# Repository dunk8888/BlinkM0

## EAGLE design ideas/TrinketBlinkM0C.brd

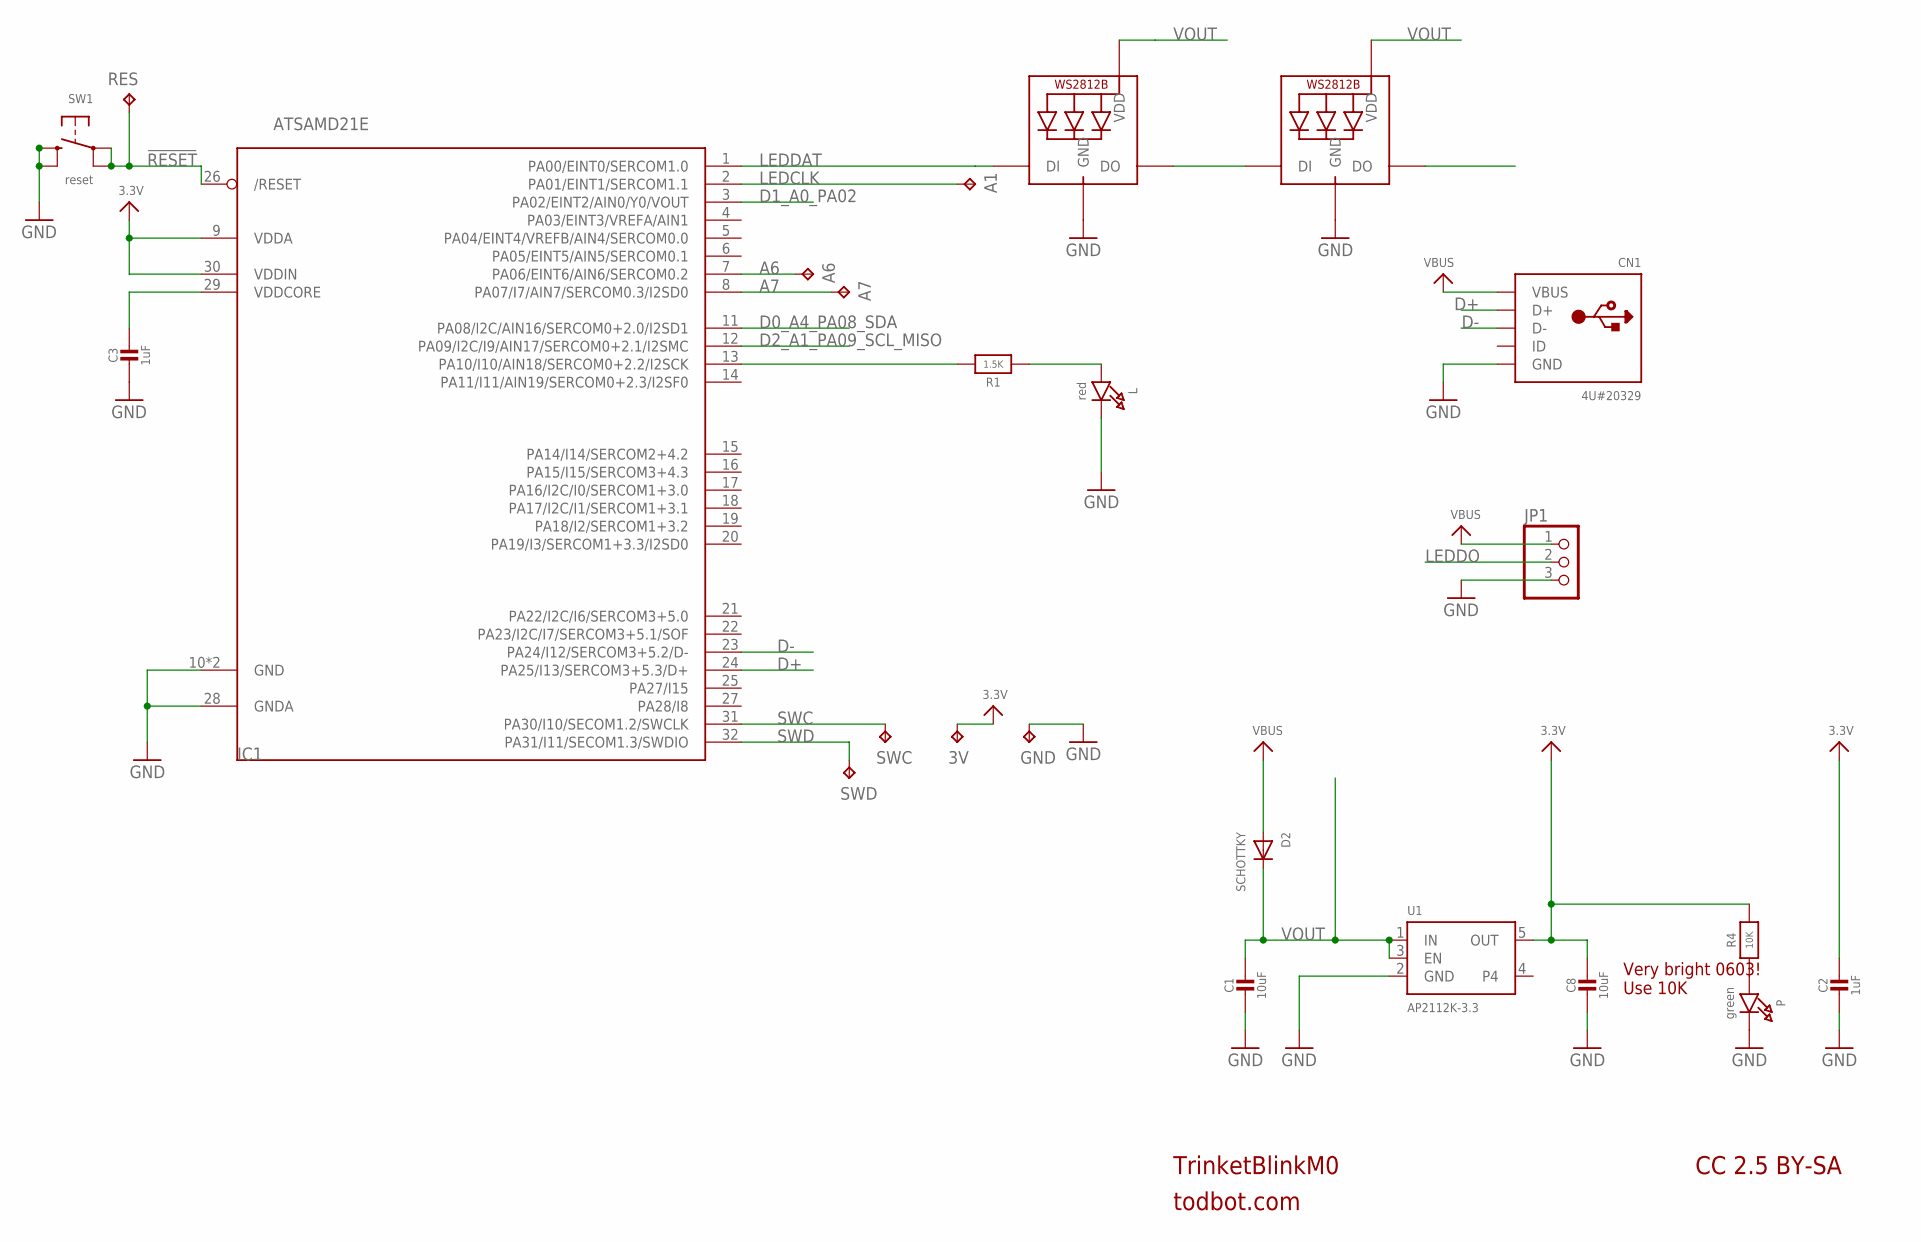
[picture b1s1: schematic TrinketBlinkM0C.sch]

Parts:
3V: TPB1,27; B1,27
A1, A6, A7: TPB1,27; B1,27
C1, C8: 10uF; 0805-NO
C2, C3: 1uF; 0603-NO
CN1: 4U#20329; 4UCONN_20329_V2
D2: SCHOTTKY; SOD-123FL
GND: TPB1,27; B1,27
IC1: ATSAMD21E; QFN32_5MM
JP1: PINHD-1X3CB; 1X03-CLEANBIG
L: red; CHIPLED_0603_NOOUTLINE
LED1, LED2: WS2812B_5050N; WS2812B-NARROW
P: green; CHIPLED_0603_NOOUTLINE
R1: 1.5K; 0603-NO
R4: 10K; 0603-NO
RES: TPB1,27; B1,27
SW1: reset; BTN_KMR2_4.6X2.8
SWC: TPB1,27; B1,27
SWD: TPB1,27; B1,27
U1: AP2112K-3.3; SOT23-5

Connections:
3.3V: 3V.TP, C2.1, C8.1, IC1.9 (VDDA), IC1.30 (VDDIN), R4.2, U1.5 (OUT)
!RESET: IC1.26 (/RESET), RES.TP, SW1.A, SW1.A' (P1)
A6: A6.TP, IC1.7 (PA06/EINT6/AIN6/SERCOM0.2)
A7: A7.TP, IC1.8 (PA07/I7/AIN7/SERCOM0.3/I2SD0)
D0_A4_PA08_SDA: IC1.11 (PA08/I2C/AIN16/SERCOM0+2.0/I2SD1)
D1_A0_PA02: IC1.3 (PA02/EINT2/AIN0/Y0/VOUT)
D2_A1_PA09_SCL_MISO: IC1.12 (PA09/I2C/I9/AIN17/SERCOM0+2.1/I2SMC)
D+: CN1.D+, IC1.24 (PA25/I13/SERCOM3+5.3/D+)
D-: CN1.D-, IC1.23 (PA24/I12/SERCOM3+5.2/D-)
GND: C1.2, C2.2, C3.2, C8.2, CN1.BASE@1 (GND), CN1.BASE@2 (GND), CN1.GND, CN1.SPRT@1 (GND), CN1.SPRT@2 (GND), CN1.SPRT@3 (GND), CN1.SPRT@4 (GND), GND.TP, IC1.10 (GND), IC1.28 (GNDA), IC1.33 (GND), JP1.3, L.C, LED1.3-GND (GND), LED2.3-GND (GND), P.C, SW1.B (S), SW1.B' (S1), U1.2 (GND)
LEDCLK: A1.TP, IC1.2 (PA01/EINT1/SERCOM1.1)
LEDDAT: IC1.1 (PA00/EINT0/SERCOM1.0), LED1.4-DIN (DI)
LEDDO: JP1.2, LED2.2-DOUT (DO)
unnamed: L.A, R1.1
unnamed: IC1.13 (PA10/I10/AIN18/SERCOM0+2.2/I2SCK), R1.2
unnamed: LED1.2-DOUT (DO), LED2.4-DIN (DI)
unnamed: P.A, R4.1
SWC: IC1.31 (PA30/I10/SECOM1.2/SWCLK), SWC.TP
SWD: IC1.32 (PA31/I11/SECOM1.3/SWDIO), SWD.TP
VBUS: CN1.VBUS, D2.A, JP1.1
VDDCORE: C3.1, IC1.29 (VDDCORE)
VOUT: C1.1, D2.C, LED1.1-VDD (VDD), LED2.1-VDD (VDD), U1.1 (IN), U1.3 (EN)

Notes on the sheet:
TrinketBlinkM0
todbot.com
CC 2.5 BY-SA
Very bright 0603! Use 10K

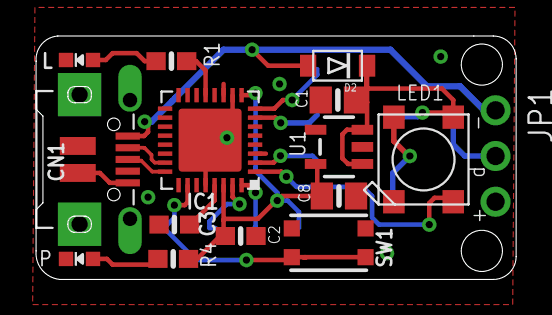
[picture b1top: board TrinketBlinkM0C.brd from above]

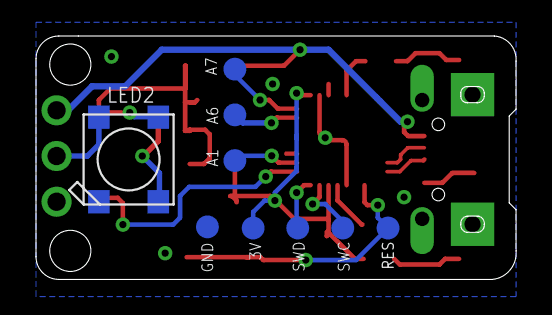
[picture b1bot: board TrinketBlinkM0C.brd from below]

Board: 2 copper layers, 26.7 x 13.5 mm, 26 parts (10 on the bottom side), 19 nets.

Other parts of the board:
U$1: TRINKET_M0_BOTTOM
U$20: TRINKET_M0_TOP

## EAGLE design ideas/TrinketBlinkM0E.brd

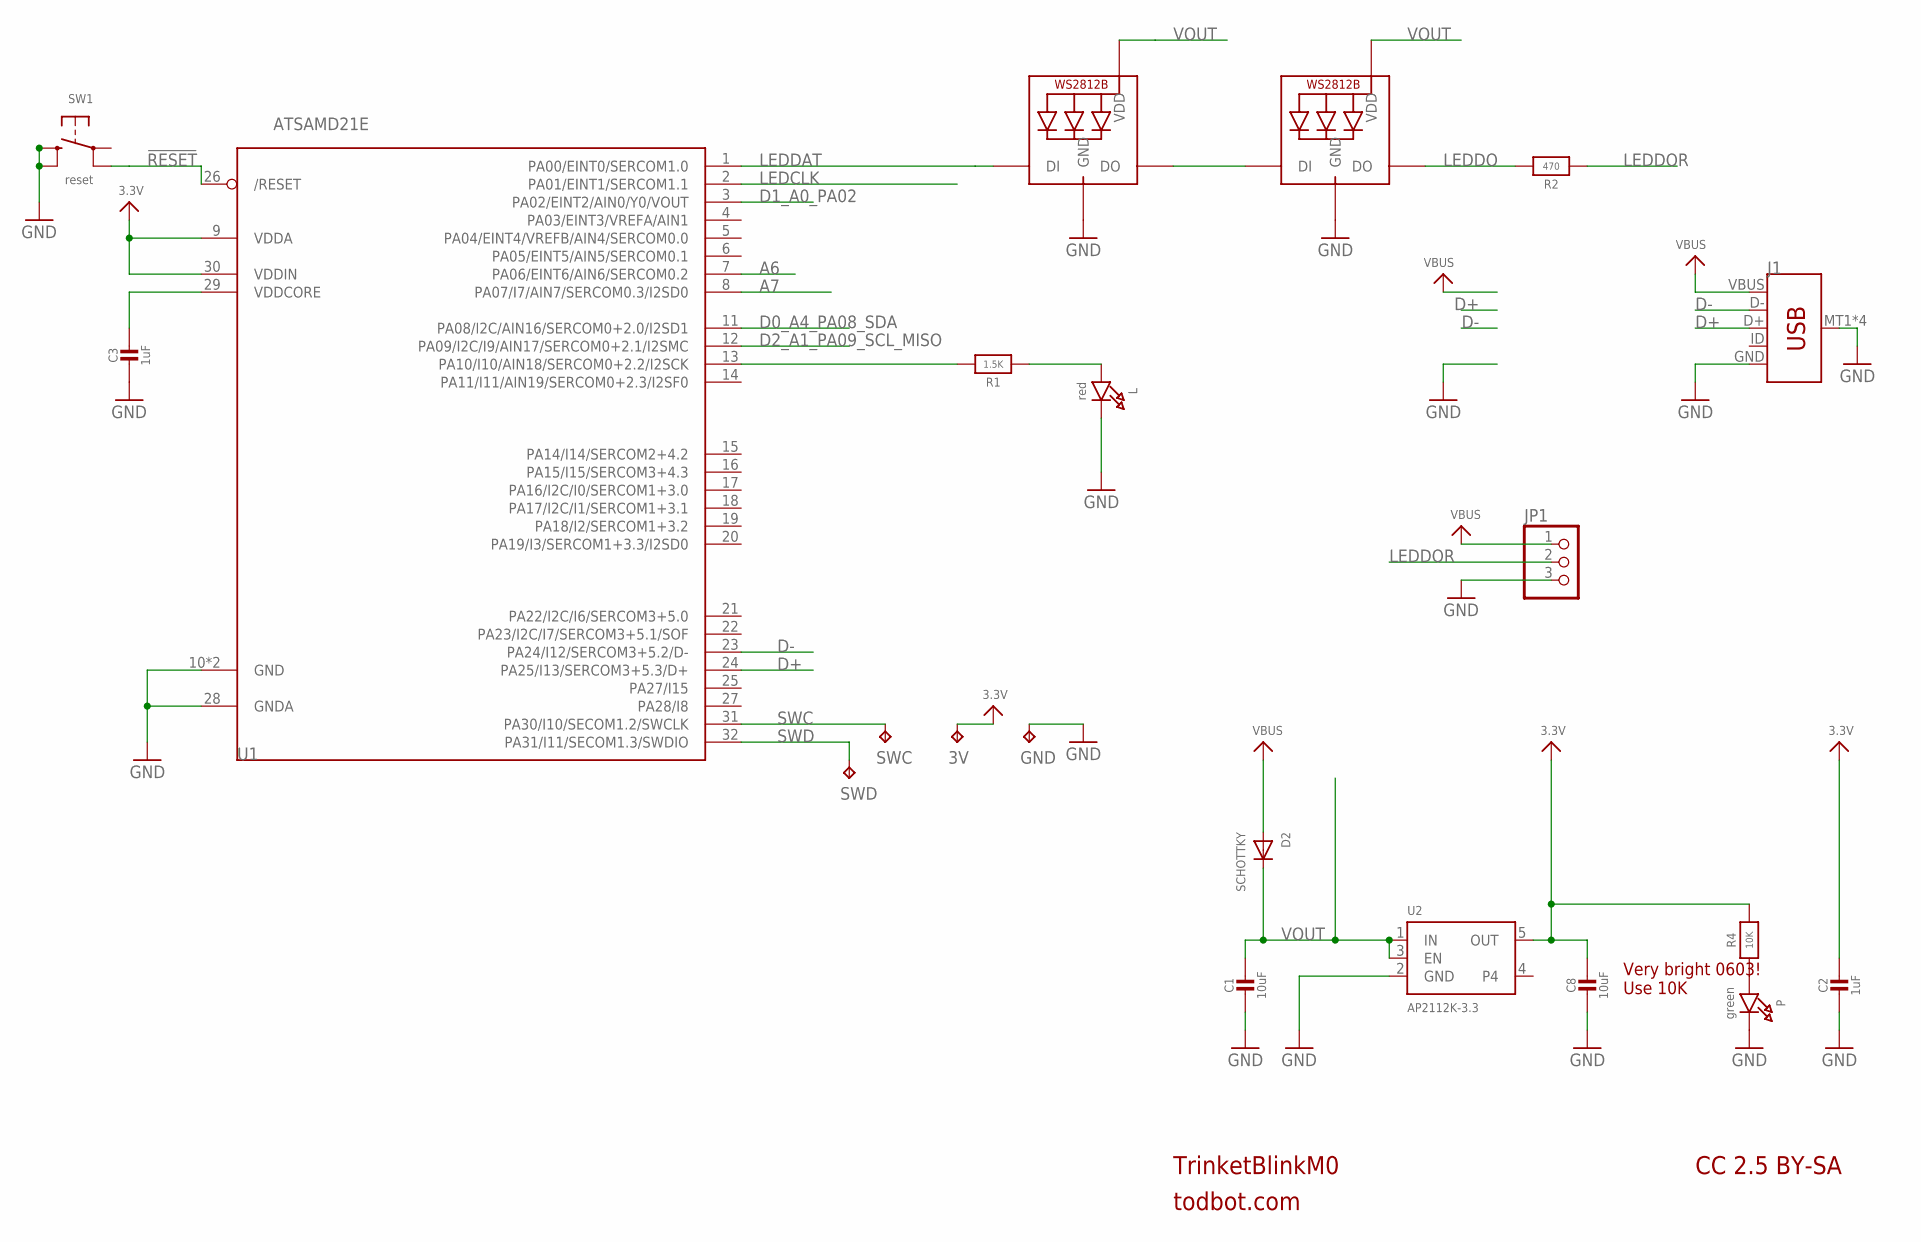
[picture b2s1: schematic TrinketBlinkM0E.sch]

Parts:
3V: TPB1,27; B1,27
C1, C8: 10uF; 0805-NO
C2, C3: 1uF; 0603-NO
D2: SCHOTTKY; SOD-123FL
GND: TPB1,27; B1,27
J1: USB_MICRO-B_SMT; USB-MICROB
JP1: PINHD-1X3CB; 1X03-CLEANBIG
L: red; CHIPLED_0603_NOOUTLINE
LED1, LED2: WS2812B_5050N; WS2812B-NARROW
P: green; CHIPLED_0603_NOOUTLINE
R1: 1.5K; 0603-NO
R2: 470; 0603-NO
R4: 10K; 0603-NO
SW1: reset; BTN_KMR2_4.6X2.8
SWC: TPB1,27; B1,27
SWD: TPB1,27; B1,27
U1: ATSAMD21E; QFN32_5MM
U2: AP2112K-3.3; SOT23-5

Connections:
3.3V: 3V.TP, C2.1, C8.1, R4.2, U1.9 (VDDA), U1.30 (VDDIN), U2.5 (OUT)
!RESET: SW1.A' (P1), U1.26 (/RESET)
A6: U1.7 (PA06/EINT6/AIN6/SERCOM0.2)
A7: U1.8 (PA07/I7/AIN7/SERCOM0.3/I2SD0)
D0_A4_PA08_SDA: U1.11 (PA08/I2C/AIN16/SERCOM0+2.0/I2SD1)
D1_A0_PA02: U1.3 (PA02/EINT2/AIN0/Y0/VOUT)
D2_A1_PA09_SCL_MISO: U1.12 (PA09/I2C/I9/AIN17/SERCOM0+2.1/I2SMC)
D+: J1.D+, U1.24 (PA25/I13/SERCOM3+5.3/D+)
D-: J1.D-, U1.23 (PA24/I12/SERCOM3+5.2/D-)
GND: C1.2, C2.2, C3.2, C8.2, GND.TP, J1.GND, J1.MT1 (SHIELD), J1.MT2 (SHIELD), J1.P$1 (SHIELD), J1.P$2 (SHIELD), JP1.3, L.C, LED1.3-GND (GND), LED2.3-GND (GND), P.C, SW1.B (S), SW1.B' (S1), U1.10 (GND), U1.28 (GNDA), U1.33 (GND), U2.2 (GND)
LEDCLK: U1.2 (PA01/EINT1/SERCOM1.1)
LEDDAT: LED1.4-DIN (DI), U1.1 (PA00/EINT0/SERCOM1.0)
LEDDO: LED2.2-DOUT (DO), R2.2
LEDDOR: JP1.2, R2.1
unnamed: L.A, R1.1
unnamed: R1.2, U1.13 (PA10/I10/AIN18/SERCOM0+2.2/I2SCK)
unnamed: LED1.2-DOUT (DO), LED2.4-DIN (DI)
unnamed: P.A, R4.1
SWC: SWC.TP, U1.31 (PA30/I10/SECOM1.2/SWCLK)
SWD: SWD.TP, U1.32 (PA31/I11/SECOM1.3/SWDIO)
VBUS: D2.A, J1.VBUS, JP1.1
VDDCORE: C3.1, U1.29 (VDDCORE)
VOUT: C1.1, D2.C, LED1.1-VDD (VDD), LED2.1-VDD (VDD), U2.1 (IN), U2.3 (EN)

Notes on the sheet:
TrinketBlinkM0
todbot.com
CC 2.5 BY-SA
Very bright 0603! Use 10K

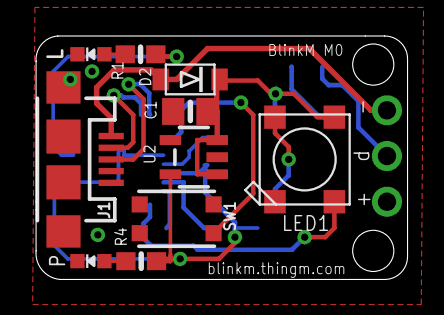
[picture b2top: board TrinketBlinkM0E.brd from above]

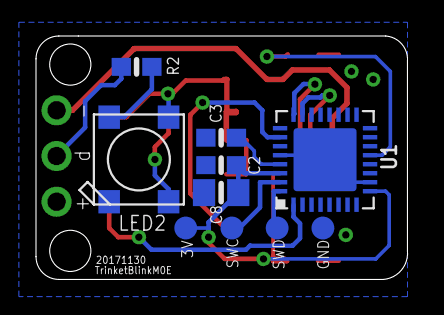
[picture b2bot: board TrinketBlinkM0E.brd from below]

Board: 2 copper layers, 20.6 x 13.5 mm, 23 parts (11 on the bottom side), 17 nets.

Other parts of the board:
U$1: TRINKET_M0_BOTTOM
U$20: TRINKET_M0_TOP

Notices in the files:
parts and their libraries:
microbuilder: This work is placed in the public domain, and may be freely used for commercial and non-commercial work with the following conditions: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
SparkFun-Connectors: Licensing: Creative Commons ShareAlike 4.0 International - https://creativecommons.org/licenses/by-sa/4.0
